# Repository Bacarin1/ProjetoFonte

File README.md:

# O projeto

O projeto consiste em uma fonte de tensão ajustável, que deve ser ligada em uma entrada de 127V de corrente alternada a 60 Hz e deve fornecer entre 3V a 12V e 100 mA
de corrente contínua

**[Vídeo explicativo](https://drive.google.com/file/d/1LYwIoo3KqqAePAGEwZrHCSvGdLBT7RUE/view?usp=sharing)**

## Grupo
- Bacarin (10873351)
- Luis Eduardo de Brito Câmara (12690282)
- Pedro Falcão Rocha (12692408)

## A fonte

Uma fonte conforme a especificação precisa de algumas etapas e componentes para funcionar. São elas:

### - O transformador
  é o que transforma a tensão de 180V de entrada em uma tensão menor, para que passe pelos demais componentes. Para
  essa fonte, foi utilizado um transformador que fornece uma tensão de saída de 24 V, mais próxima dos 12V que queremos.
  Agora que temos valores menores para trabalhar, podemos nos preocupar em deixar a corrente contínua
 
### - A retificação
  é a primeira etapa para transformar AC em DC. A retificação faz com que a corrente alternada se torne uma corrente polarizada, removendo
  os "vales" da tensão de entrada e deixando apenas cristas.  

  Senoide da fonte antes da retificação
  
  A retificação nessa fonte é feita por meio de uma ponte de diodos - que fazem com que a corrente flua em apenas um sentido (caso a sua tensão máxima não seja rompida)

  onda após a retificação
  
  É importante notar que cada diodo consome 0,7V da tensão, portanto nossa tensão anterior de 24V, nesse
  ponto, já caiu levemente para 22,6V (apenas dois diodos são usados por vez)
  
  Agora, o objetivo é deixar essa tensão com apenas cristas o mais estável possível
  
### - A filtragem
  é a etapa em que a tensão é filtrada para transformar a corrente em DC - corrente contínua - com menos oscilações.
  O principal responsável por essa etapa é o capacitor. Funciona da seguinte forma:
  O capacitor, em paralelo com o circuito que temos até agora, é carregado quando os diodos deixam a corrente passar, e, na falta
  de corrente, os momentos baixos do gráfico anterior, age como uma fonte para o resto do circuito.
  Para essa finalidade, quanto maior fosse a capacitância do capacitor, melhor seria, pois ele forneceria
  tensão suficiente para que o ripple, a variação de tensão, fosse mínima. Mas na prática, não se pode
  usar um capacitor tão grande, tanto pelo custo quanto pelo tamanho. Então o quão grande precisa ser o capacitor? O suficiente para que ele gere um ripple de no
  máximo 10% da tensão que ele recebe. Encontramos esse valor pela seguinte fórmula:

 a qual nos diz que um capacitor de 370 µF é suficiente. Vamos então escolher um capacitor de valor comercial um pouco acima desse. Na loja em que estamos comprando, o mais
 próximo é o de 470 µF.
  
### - A regulação
  etapa em que a corrente recebe _tweaks_ para ficar conforme a especificação. Nessa etapa, é utilizado o diodo zener. Em diodos comuns, quando se atinge a tensão de ruptura, eles passam a deixar uma corrente extremamente grande passar por eles no sentido inverso. No diodo zener, quando se atinge uma tensão chamada tensão zener, ele passa a permitir a passagem de correntes de forma a manter constante a tensão entre seus terminais, agindo como um curto circuito. Isso tem como efeito, no circuito, "cortar" a tensão extra que tinhamos para o valor de sua tensão zener. Como queremos uma tensão de 12V, podemos usar o modelo comercial de Zener de 13V, logo acima disso. Precisamos também ligar um resistor em série com o zener, para que ele não queime.
  
  Partimos então da escolha de um diodo zener de tensão Vz = 13V, e que tem como potência máxima 1 W. Vamos escolher um resistor de forma que a potência máxima dissipada pelo zener seja de 0,5 W, para dar certa margem. Temos, então, que:

Essa é a resistência mínima que o resistor pode ter. Testando resistências acima disso, descobrimos que o circuito continua fornecendo uma tensão estável quando colocamos um resistor de até 2,7kΩ, então vamos escolher um desses. A vantagem é que, quanto maior esse resistor, menos corrente passa pelo diodo zener, e, como efeito, ele gasta menos potência e esquenta menos.

### - O circuito final no Falstad

[link para o circuito no Falstad](https://tinyurl.com/ydmfa28s)

A montagem foi feita no simulador, o que forneceu os valores necessários de cada componente. Alguns outros componentes foram usados no circuito, e estão listados abaixo

  - Transistor bipolar: ligado da forma que está no circuito, ele controla e amplifica a corrente que chegará na carga
  - Potenciômetro: é usado para controlar a tensão no terminal de saída, variando de 3V a 12V
  - Resistor de 2.2KΩ: regula a voltagem do circuito

### - A montagem no software Eagle

Esquemático

PCB
  
 ### - Componentes e preços
 Abaixo vai uma tabela com os componentes usados, suas especificações, preços e links
 
 |Nome do Componente |Especificações|Preço R$ |
 |-------------------|--------------|------|
 |Transformador|trafo que transforma entradas de 110 ou 220 V em 24 V, com corrente de 1A|[38,77](https://www.baudaeletronica.com.br/transformador-trafo-1a-24v.html)|
 |Capacitor eletrolítico|470uF / 25V|[0,41](https://www.baudaeletronica.com.br/capacitor-eletrolitico-470uf-25v.html)|
 |Resistor 2.2k|2.2 kΩ, 2W de potência|[0,38](https://www.baudaeletronica.com.br/resistor-2k2-5-2w.html)|
 |Resistor 2.7k|2.7 Ω, 1/2W de potência|[0,14](https://www.baudaeletronica.com.br/resistor-2k7-1-2w.html)|
 |Potenciômetro|Potenciômetro linear de 5000Ω|[1,99](https://www.baudaeletronica.com.br/potenciometro-linear-de-5k-5000.html)|
 |Diodo Zener|1N4743, de 13V e 1 W|[0,19](https://www.baudaeletronica.com.br/diodo-zener-1n4743-13v-1w.html)|
 |Diodo retificador|1N5404, de 3A|4 x [0,34](https://www.baudaeletronica.com.br/diodo-1n5404.html)|
 |Transistor NPN BC337|tensão máxima de 45V e corrente máxima IC de 500mA|[0,20](https://www.baudaeletronica.com.br/transistor-npn-bc337.html)|
 ||total|R$ 43,44

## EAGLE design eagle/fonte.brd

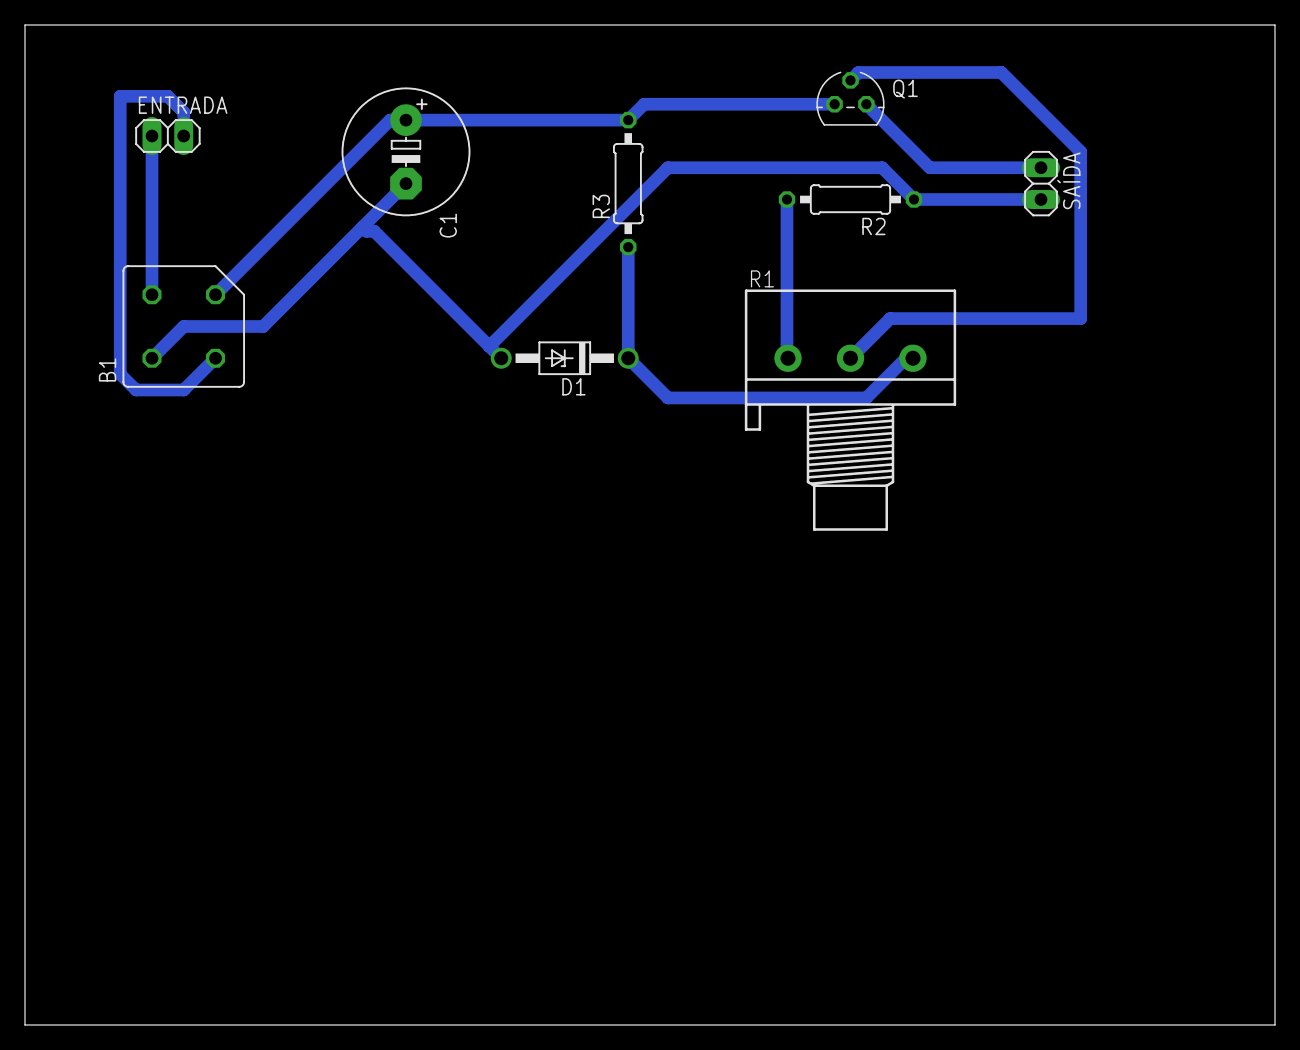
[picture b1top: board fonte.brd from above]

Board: 2 copper layers, 100.0 x 80.0 mm, 9 parts (0 on the bottom side), 8 nets.

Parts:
B1: 1KAB
C1: 470uF; E5-10,5
D1: 1N4728; DO41Z10
ENTRADA: 1X02
Q1: BC547; TO92
R1: 5KΩ; 3RP/1610N
R2: 2.2kΩ; 0207/10
R3: 240Ω; 0207/10
SAÍDA: 1X02

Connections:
unnamed: R1.1, R2.2
unnamed: D1.C, R1.3, R3.1
unnamed: Q1.2, R1.2
unnamed: B1.AC1, ENTRADA.2
unnamed: B1.AC2, ENTRADA.1
unnamed: B1.-, C1.-, D1.A, R2.1, SAÍDA.2
unnamed: B1.+, C1.+, Q1.3, R3.2
unnamed: Q1.1, SAÍDA.1

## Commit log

2021-07-23 cria etapasFonte.md na versão 1
2021-07-23 update no readme
2021-07-24 mano
2021-07-24 adiciona cálculos
2021-07-24 correções
2021-07-24 novos valores de transformador
    e alterações nas contas
2021-07-24 correção transformador
2021-07-24 correção do capacitor
2021-07-24 esquemático incial da fonte
2021-07-27 corrige o valor do resistor
2021-07-27 atualizando função do transistor
2021-07-27 corrige diodo
2021-07-29 update readme
    tirando o resistor da carga no circuito do falstad
